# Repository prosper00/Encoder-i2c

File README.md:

simple ch32v003 firmware to read a rotary encoder input device, and convert it to i2c.

Usage / notes
- configured for a CH32V003 SOP8 package
- encoder inputs are connected to PA1 and PA2
- encoder pushbutton is connected to PC4
- all encoder pins are externally RC debounced and pulled up [todo: add schematic]
- device is configured as an i2c slave device on address 0x09.
- 'read' two bytes: the first byte is the rotation value, and the second byte indicates whether the button has been pressed
- values are reset to zero after a read
- no software debounce or acceleration scaling has been implemented
- i2c writes not currently implemented. TODO: update this firmware for a 20-pin package, and use writes to light LEDs

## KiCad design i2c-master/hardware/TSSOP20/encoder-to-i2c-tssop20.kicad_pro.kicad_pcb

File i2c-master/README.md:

simple ch32v003 firmware to read a rotary encoder input device, and convert it to i2c.

Usage / notes
- configured for a CH32V003 SOP8 package
- encoder inputs are connected to PA1 and PA2
- encoder pushbutton is connected to PC4
- all encoder pins are externally RC debounced and pulled up [ see /hardware for schematic ]
- device is configured as an i2c slave device on address 0x09.
- 'read' two bytes: the first byte is the rotation value, and the second byte indicates whether the button has been pressed
- values are reset to zero after a read
- no software debounce or acceleration scaling has been implemented
- i2c writes not currently implemented. TODO: update this firmware for a 20-pin package, and use writes to light LEDs

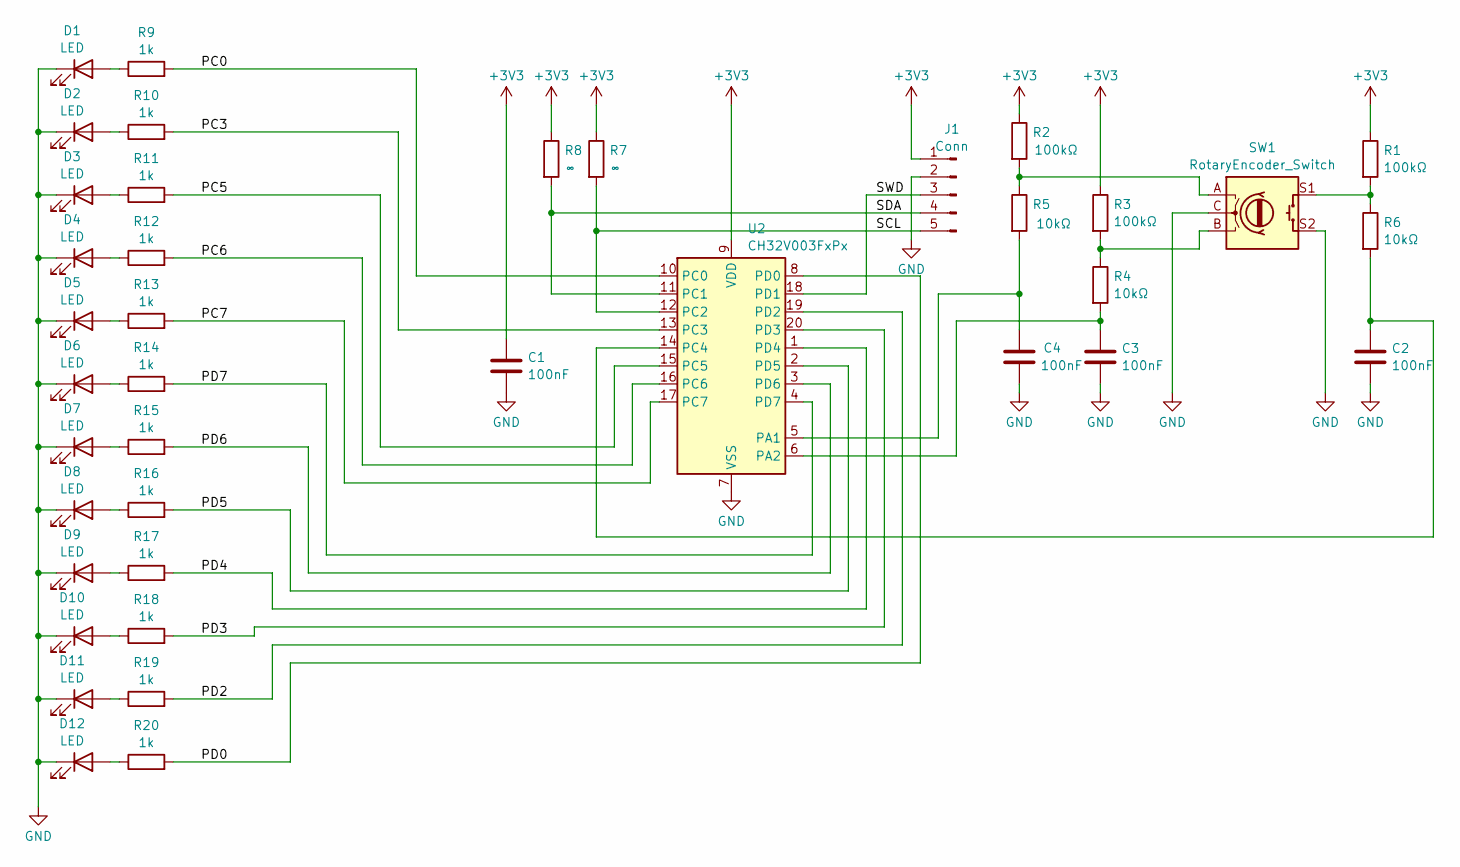
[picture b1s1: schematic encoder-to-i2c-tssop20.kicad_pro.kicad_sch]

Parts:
C1, C2, C3, C4: 100nF; C_0603_1608Metric_Pad1.08x0.95mm_HandSolder
D1, D2, D3, D4, D5, D6, D7, D8, D9, D10, D11, D12: LED; LED_0603_1608Metric_Pad1.05x0.95mm_HandSolder
J1: Conn; JST_XH_B5B-XH-A_1x05_P2.50mm_Vertical
R1, R2, R3: 100kΩ; R_0603_1608Metric_Pad0.98x0.95mm_HandSolder
R4, R5, R6: 10kΩ; R_0603_1608Metric_Pad0.98x0.95mm_HandSolder
R7, R8: ∞; R_0603_1608Metric_Pad0.98x0.95mm_HandSolder
R9, R10, R11, R12, R13, R14, R15, R16, R17, R18, R19, R20: 1k; R_0603_1608Metric_Pad0.98x0.95mm_HandSolder
SW1: RotaryEncoder_Switch; RotaryEncoder_Bourns_Vertical_PEC12R-3x17F-Sxxxx
U2: CH32V003FxPx; TSSOP-20_4.4x6.5mm_P0.65mm

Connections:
+3V3: C1.1, J1.1, R1.1, R2.1, R3.1, R7.1, R8.1, U2.9 (VDD)
/PC0: R9.2, U2.10 (PC0)
/PC3: R10.2, U2.13 (PC3)
/PC5: R11.2, U2.15 (PC5)
/PC6: R12.2, U2.16 (PC6)
/PC7: R13.2, U2.17 (PC7)
/PD0: R20.2, U2.8 (PD0)
/PD2: R19.2, U2.19 (PD2)
/PD3: R18.2, U2.20 (PD3)
/PD4: R17.2, U2.1 (PD4)
/PD5: R16.2, U2.2 (PD5)
/PD6: R15.2, U2.3 (PD6)
/PD7: R14.2, U2.4 (PD7)
/SCL: J1.5, R7.2, U2.12 (PC2)
/SDA: J1.4, R8.2, U2.11 (PC1)
/SWD: J1.3, U2.18 (PD1)
GND: C1.2, C2.2, C3.2, C4.2, D1.1 (K), D2.1 (K), D3.1 (K), D4.1 (K), D5.1 (K), D6.1 (K), D7.1 (K), D8.1 (K), D9.1 (K), D10.1 (K), D11.1 (K), D12.1 (K), J1.2, SW1.C, SW1.S2, U2.7 (VSS)
unnamed: D1.2 (A), R9.1
unnamed: D2.2 (A), R10.1
unnamed: D3.2 (A), R11.1
unnamed: D4.2 (A), R12.1
unnamed: D5.2 (A), R13.1
unnamed: D6.2 (A), R14.1
unnamed: D7.2 (A), R15.1
unnamed: D8.2 (A), R16.1
unnamed: D9.2 (A), R17.1
unnamed: D10.2 (A), R18.1
unnamed: D11.2 (A), R19.1
unnamed: D12.2 (A), R20.1
unnamed: R1.2, R6.1, SW1.S1
unnamed: R2.2, R5.1, SW1.A
unnamed: R3.2, R4.1, SW1.B
unnamed: C4.1, R5.2, U2.5 (PA1)
unnamed: C3.1, R4.2, U2.6 (PA2)
unnamed: C2.1, R6.2, U2.14 (PC4)

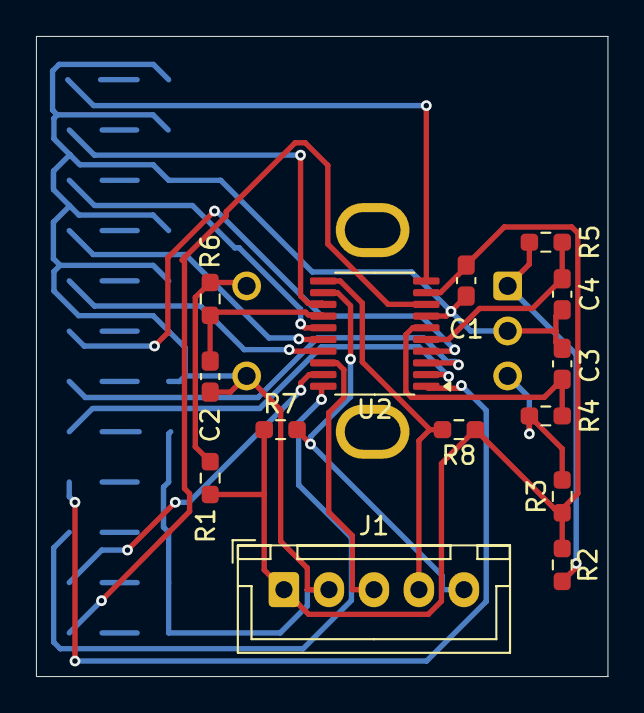
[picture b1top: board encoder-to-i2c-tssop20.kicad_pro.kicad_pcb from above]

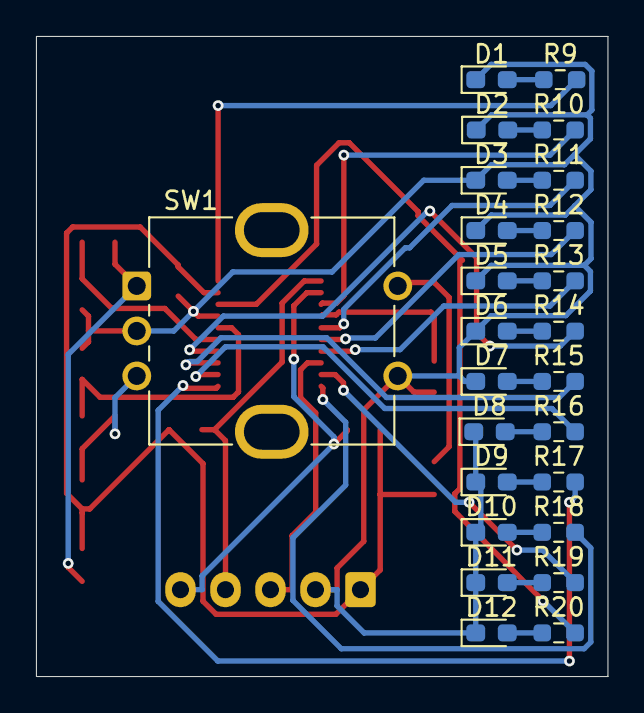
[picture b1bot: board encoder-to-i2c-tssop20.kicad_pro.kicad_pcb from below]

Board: 2 copper layers, 31.8 x 35.6 mm, 39 parts (25 on the bottom side), 35 nets.

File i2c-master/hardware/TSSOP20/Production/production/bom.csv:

Designator,Footprint,Quantity,Value,LCSC Part #
"C1_6, C1_5, C1_4, C1_3, C1_2, C1, C2_6, C2_5, C2_4, C2_3, C2_2, C2, C3_6, C3_5, C3_4, C3_3, C3_2, C3, C4_6, C4_5, C4_4, C4_3, C4_2, C4",0603,24,100nF,
"D1_6, D1_5, D1_4, D1_3, D1_2, D1, D10_6, D10_5, D10_4, D10_3, D10_2, D10, D11_6, D11_5, D11_4, D11_3, D11_2, D11, D12_6, D12_5, D12_4, D12_3, D12_2, D12, D2_6, D2_5, D2_4, D2_3, D2_2, D2, D3_6, D3_5, D3_4, D3_3, D3_2, D3, D4_6, D4_5, D4_4, D4_3, D4_2, D4, D5_6, D5_5, D5_4, D5_3, D5_2, D5, D6_6, D6_5, D6_4, D6_3, D6_2, D6, D7_6, D7_5, D7_4, D7_3, D7_2, D7, D8_6, D8_5, D8_4, D8_3, D8_2, D8, D9_6, D9_5, D9_4, D9_3, D9_2, D9",0603,72,LED,
"J1_6, J1_5, J1_4, J1_3, J1_2, J1",JST_XH_B5B-XH-A_1x05_P2.50mm_Vertical,6,Conn,
"R1_6, R1_5, R1_4, R1_3, R1_2, R1, R2_6, R2_5, R2_4, R2_3, R2_2, R2, R3_6, R3_5, R3_4, R3_3, R3_2, R3",0603,18,100kΩ,
"R10_6, R10_5, R10_4, R10_3, R10_2, R10, R11_6, R11_5, R11_4, R11_3, R11_2, R11, R12_6, R12_5, R12_4, R12_3, R12_2, R12, R13_6, R13_5, R13_4, R13_3, R13_2, R13, R14_6, R14_5, R14_4, R14_3, R14_2, R14, R15_6, R15_5, R15_4, R15_3, R15_2, R15, R16_6, R16_5, R16_4, R16_3, R16_2, R16, R17_6, R17_5, R17_4, R17_3, R17_2, R17, R18_6, R18_5, R18_4, R18_3, R18_2, R18, R19_6, R19_5, R19_4, R19_3, R19_2, R19, R20_6, R20_5, R20_4, R20_3, R20_2, R20, R9_6, R9_5, R9_4, R9_3, R9_2, R9",0603,72,1k,
"R4_6, R4_5, R4_4, R4_3, R4_2, R4, R5_6, R5_5, R5_4, R5_3, R5_2, R5, R6_6, R6_5, R6_4, R6_3, R6_2, R6",0603,18,10kΩ,
"R7_6, R7_5, R7_4, R7_3, R7_2, R7, R8_6, R8_5, R8_4, R8_3, R8_2, R8",0603,12,∞,
"SW1_6, SW1_5, SW1_4, SW1_3, SW1_2, SW1",RotaryEncoder_Bourns_Vertical_PEC12R-3x17F-Sxxxx,6,RotaryEncoder_Switch,
"U2_6, U2_5, U2_4, U2_3, U2_2, U2",TSSOP-20_4.4x6.5mm_P0.65mm,6,CH32V003FxPx,

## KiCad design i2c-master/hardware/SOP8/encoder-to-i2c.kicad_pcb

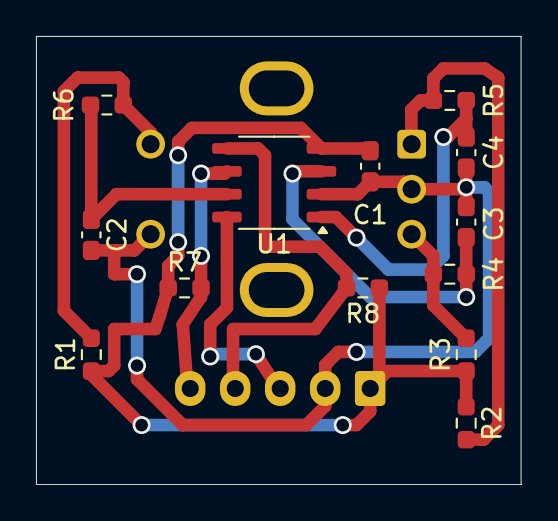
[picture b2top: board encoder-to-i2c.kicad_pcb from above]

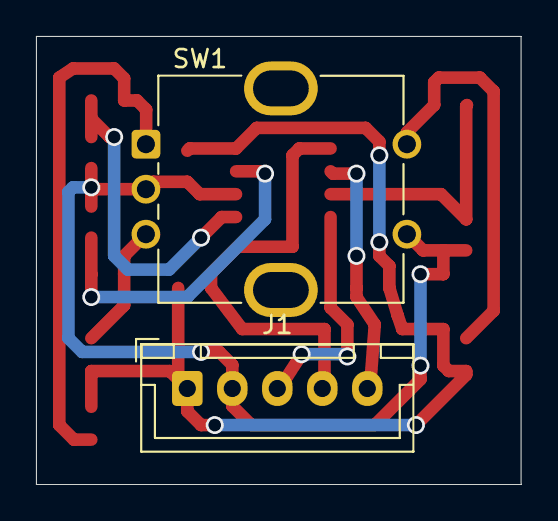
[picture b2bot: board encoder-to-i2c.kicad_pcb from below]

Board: 2 copper layers, 26.9 x 24.9 mm, 15 parts (2 on the bottom side), 11 nets.

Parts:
C1, C3, C4: 100n; C_0603_1608Metric_Pad1.08x0.95mm_HandSolder
C2: 100nF; C_0603_1608Metric_Pad1.08x0.95mm_HandSolder
J1: Conn; JST_XH_B5B-XH-A_1x05_P2.50mm_Vertical
R1, R2, R3: 100kΩ; R_0603_1608Metric_Pad0.98x0.95mm_HandSolder
R4, R5, R6: 10kΩ; R_0603_1608Metric_Pad0.98x0.95mm_HandSolder
R7, R8: ∞; R_0603_1608Metric_Pad0.98x0.95mm_HandSolder
SW1: RotaryEncoder_Switch; RotaryEncoder_Bourns_Vertical_PEC12R-3x17F-Sxxxx
U1: CH32V003JxMx; SOP-8_3.9x4.9mm_P1.27mm

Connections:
+3V3: C1.1, J1.1, R1.1, R2.1, R3.1, R7.1, R8.1, U1.4 (VDD)
/SCL: J1.5, R7.2, U1.6 (PC2)
/SDA: J1.4, R8.2, U1.5 (PC1)
/SWD: J1.3, U1.8 (PD1/PD4/PD5)
GND: C1.2, C2.2, C3.2, C4.2, J1.2, SW1.C, SW1.S2, U1.2 (VSS)
unnamed: R1.2, R6.1, SW1.S1
unnamed: R2.2, R5.1, SW1.A
unnamed: R3.2, R4.1, SW1.B
unnamed: C3.1, R4.2, U1.3 (PA2)
unnamed: C2.1, R6.2, U1.7 (PC4)
unnamed: C4.1, R5.2, U1.1 (PD6/PA1)

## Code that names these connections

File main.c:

/* Template app on which you can build your own. */
// #pragma GCC optimize( "O3" )

#include "ch32v003fun.h"
#include "exti_pin_change_isr.h"
#include "i2c_slave.h"
#include <stdio.h>

// read and write buffers for i2c
// we are an i2c slave device, so a 'write' is INBOUND data (MOSI)
// and a 'read' is outbound data (MISO)
volatile uint8_t i2c_read_registers[2] = { 0x00 }; // [0] is the encoder rotation and [1] is the button status
volatile uint8_t i2c_write_registers[2] = { 0x00 }; // eventually, I'll use this to set LEDs

// callback function to handle i2c write requests
void onWrite( uint8_t reg, uint8_t length )
{
	// set LEDs on the board. Not implemented on the SOIC-8 device - insufficient pins
}

// callback function to handle i2c read requests
// called *after* the data is sent out
void onRead( uint8_t reg )
{
	i2c_read_registers[reg] = 0; // clear the buffers once it's been transmitted
}

void i2c_Init( void )
{
	// Initialize I2C slave
	funPinMode( PC1, GPIO_CFGLR_OUT_10Mhz_AF_OD ); // SDA
	funPinMode( PC2, GPIO_CFGLR_OUT_10Mhz_AF_OD ); // SCL
	SetupI2CSlave( I2CADDR, i2c_read_registers, sizeof( i2c_read_registers ), i2c_write_registers,
		sizeof( i2c_write_registers ), onWrite, onRead, false );
}

void Exti_Init( void )
{
	// Assumes all encoder pins are externally pulled up.
	// PA1 and PA2 are encoder inputs
	funPinMode( PA1, GPIO_CFGLR_IN_FLOAT );
	funPinMode( PA2, GPIO_CFGLR_IN_FLOAT );

	// PC4 is encoder button
	funPinMode( PC4, GPIO_CFGLR_IN_FLOAT );

	// Configure the PA1 and PC4 as an interrupt.
	AFIO->EXTICR = ( AFIO_EXTICR1_EXTI1_PA | AFIO_EXTICR_EXTI4_PC );
	// Enable the interrupt channels
	EXTI->INTENR = ( EXTI_INTENR_MR1 | EXTI_INTENR_MR4 ); // Enable EXT line 1 and 4
	EXTI->FTENR = ( EXTI_FTENR_TR1 | EXTI_FTENR_TR4 ); // Falling edge trigger on channels/pins 1 and 4

	// enable interrupt
	NVIC_EnableIRQ( EXTI7_0_IRQn );
}

const uint8_t LEDS[12] = { PC0, PC3, PC5, PC6, PC7, PD7, PD6, PD5, PD4, PD3, PD2, PD0 };

void LEDS_Init( void )
{
	for ( uint8_t i = 0; i < sizeof( LEDS ); i++ )
	{
		funPinMode( LEDS[i], GPIO_CFGLR_OUT_2Mhz_PP );
	}
}

void LEDsoff( void )
{
	for ( uint8_t i = 0; i < sizeof( LEDS ); i++ )
	{
		funDigitalWrite( LEDS[i], FUN_LOW );
	}
}

void LEDson( void )
{
	for ( uint8_t i = 0; i < sizeof( LEDS ); i++ )
	{
		funDigitalWrite( LEDS[i], FUN_HIGH );
	}
}

// updateLEDs(uint16_t) - activates the LED indicated by each bit position in the argument
//  i.e. bit 0 == LED 0 'on'
void updateLEDs( uint16_t num )
{
	LEDsoff();

	for ( int i = 0; i < 12; i++ )
	{
		if ( num & 1 )
		{
			funDigitalWrite( LEDS[i], FUN_HIGH );
		}
		num >>= 1;
	}
}

void blip( void )
{

	for ( int i = 0; i <= 12; i++ )
	{
		updateLEDs( 1 << i );
		Delay_Ms( 8 );
	}
	LEDsoff();

	for ( int i = 10; i >= 0; i-- )
	{
		updateLEDs( 1 << i );
		Delay_Ms( 8 );
	}
	LEDsoff();
}

int main( void )
{
	SystemInit();
	funGpioInitAll();

	Exti_Init();
	i2c_Init();
	LEDS_Init();

	int8_t count = 0;
	bool off = false;

	blip();
	updateLEDs( 1 );

	while ( 1 )
	{
		__WFI(); // halt until an event comes in
		// printf( "got: %2x %2x \n", i2c_read_registers[0], i2c_read_registers[1] );

		if ( encoder_button_event )
		{
			if ( off )
			{
				blip();
				updateLEDs( 1 << count );
			}
			else
				blip();
			off = !off;
		}

		count += encoder_direction;
		if ( count >= 11 ) count = 11;
		if ( count <= 0 ) count = 0;
		if ( encoder_direction )
		{
			updateLEDs( 1 << count );
			off = false;
		}

		encoder_direction = 0;
		encoder_button_event = 0;

		// put the encoder data into the i2c queue to send
		i2c_read_registers[0] = count;
		i2c_read_registers[1] = !off;
	}
}

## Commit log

2024-04-29 Added schematic and PCB
2024-05-17 Added gerbers and an i2c master implementation
2024-06-05 added LEDs
